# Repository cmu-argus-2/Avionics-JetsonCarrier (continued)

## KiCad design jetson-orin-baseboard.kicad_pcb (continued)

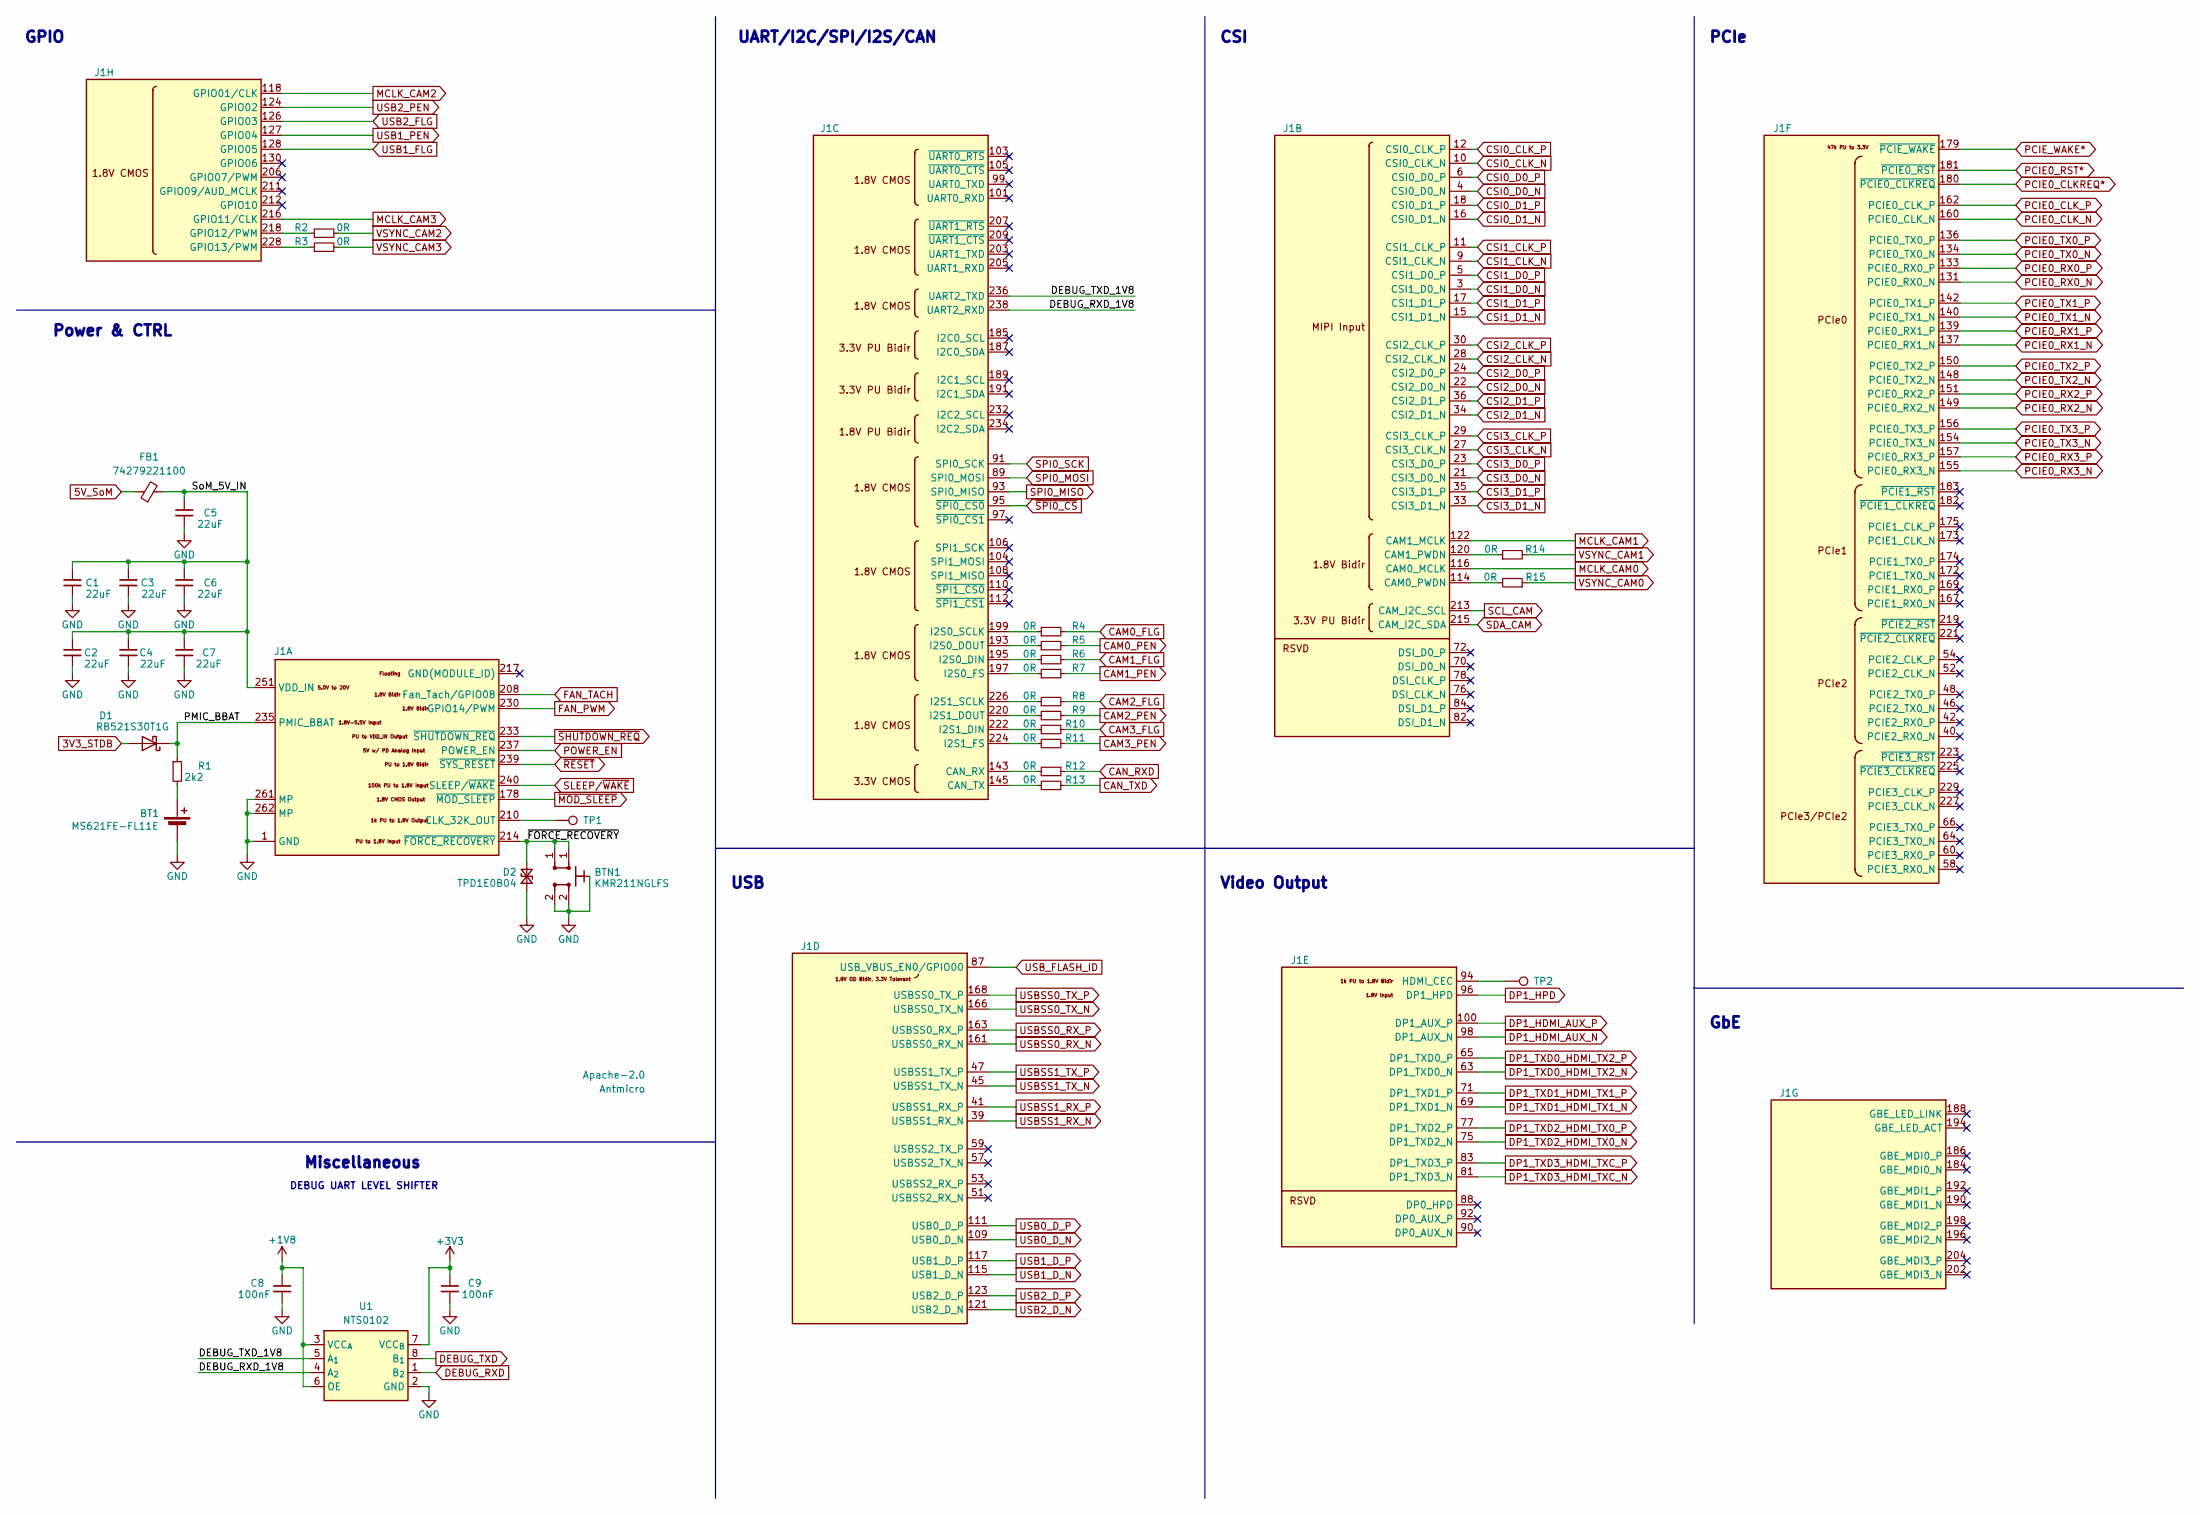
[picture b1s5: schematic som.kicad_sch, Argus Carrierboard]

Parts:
BT1: MS621FE-FL11E; MPN MS621FE-FL11E
BTN1: KMR211NGLFS; SW_Push_1P1T-SH_NO_CK_KMR2xxG; MPN C221676; LCSC C221676
C1, C2, C3, C4, C5, C6, C7: 22uF; C_0603_1608Metric; MPN C2762594; LCSC C84419
C8, C9: 100nF; C_0603_1608Metric; MPN C307348; LCSC C14663
D1: RB521S30T1G; D_SOD-523; MPN RB521S30T1G; LCSC C145179
D2: TPD1E0B04; Texas_DPY0002A_0.6x1mm_P0.65mm; MPN C1975594; LCSC C1975594
FB1: 74279221100; L_1206_3216Metric; MPN C5355985; LCSC C5355985
J1: Bus_DDR4_SODIMM_CUSTOM_Jetson-Orin-H9.2mm-socket; Jetson_Module_TE_2309409-1; MPN 2309413-1; LCSC C5164025
R1: 2k2; R_0603_1608Metric; MPN C2076947; LCSC C4190
R2, R3, R4, R5, R6, R7, R8, R9, R10, R11, R12, R13, R14, R15: 0R; R_0402_1005Metric; MPN C190119; LCSC C17168
TP1, TP2: TP_0.75mm_SMD; TestPoint_Pad_D1.0mm
U1: NTS0102; NXP_XSON-8; MPN NTS0102GT; LCSC C2687851

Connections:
3V3_STDB: D1.2 (A); also elsewhere on the board
5V_SoM: FB1.1; also elsewhere on the board
+1V8: C8.1, U1.3 (VCC_{A}), U1.6 (OE); also elsewhere on the board
+3V3: C9.1, U1.7 (VCC_{B}); also elsewhere on the board
/SoM/DEBUG_RXD_1V8: J1.238 (UART2_RXD), U1.4 (A_{2})
/SoM/DEBUG_TXD_1V8: J1.236 (UART2_TXD), U1.5 (A_{1})
/SoM/PMIC_BBAT: D1.1 (K), J1.235 (PMIC_BBAT), R1.1
/SoM/SoM_5V_IN: C1.1, C2.1, C3.1, C4.1, C5.1, C6.1, C7.1, FB1.2, J1.251 (VDD_IN), J1.252 (VDD_IN), J1.253 (VDD_IN), J1.254 (VDD_IN), J1.255 (VDD_IN), J1.256 (VDD_IN), J1.257 (VDD_IN), J1.258 (VDD_IN), J1.259 (VDD_IN), J1.260 (VDD_IN)
/SoM/~FORCE_RECOVERY: BTN1.1, D2.2 (A2), J1.214 (~FORCE_RECOVERY)
CAM0_FLG: R4.2; also elsewhere on the board
CAM0_PEN: R5.2; also elsewhere on the board
CAM1_FLG: R6.2; also elsewhere on the board
CAM1_PEN: R7.2; also elsewhere on the board
CAM2_FLG: R8.2; also elsewhere on the board
CAM2_PEN: R9.2; also elsewhere on the board
CAM3_FLG: R10.2; also elsewhere on the board
CAM3_PEN: R11.2; also elsewhere on the board
CAN_RXD: R12.2; also elsewhere on the board
CAN_TXD: R13.2; also elsewhere on the board
CSI0_CLK_N: J1.10 (CSI0_CLK_N); also elsewhere on the board
CSI0_CLK_P: J1.12 (CSI0_CLK_P); also elsewhere on the board
CSI0_D0_N: J1.4 (CSI0_D0_N); also elsewhere on the board
CSI0_D0_P: J1.6 (CSI0_D0_P); also elsewhere on the board
CSI0_D1_N: J1.16 (CSI0_D1_N); also elsewhere on the board
CSI0_D1_P: J1.18 (CSI0_D1_P); also elsewhere on the board
CSI1_CLK_N: J1.9 (CSI1_CLK_N); also elsewhere on the board
CSI1_CLK_P: J1.11 (CSI1_CLK_P); also elsewhere on the board
CSI1_D0_N: J1.3 (CSI1_D0_N); also elsewhere on the board
CSI1_D0_P: J1.5 (CSI1_D0_P); also elsewhere on the board
CSI1_D1_N: J1.15 (CSI1_D1_N); also elsewhere on the board
CSI1_D1_P: J1.17 (CSI1_D1_P); also elsewhere on the board
CSI2_CLK_N: J1.28 (CSI2_CLK_N); also elsewhere on the board
CSI2_CLK_P: J1.30 (CSI2_CLK_P); also elsewhere on the board
CSI2_D0_N: J1.22 (CSI2_D0_N); also elsewhere on the board
CSI2_D0_P: J1.24 (CSI2_D0_P); also elsewhere on the board
CSI2_D1_N: J1.34 (CSI2_D1_N); also elsewhere on the board
CSI2_D1_P: J1.36 (CSI2_D1_P); also elsewhere on the board
CSI3_CLK_N: J1.27 (CSI3_CLK_N); also elsewhere on the board
CSI3_CLK_P: J1.29 (CSI3_CLK_P); also elsewhere on the board
CSI3_D0_N: J1.21 (CSI3_D0_N); also elsewhere on the board
CSI3_D0_P: J1.23 (CSI3_D0_P); also elsewhere on the board
CSI3_D1_N: J1.33 (CSI3_D1_N); also elsewhere on the board
CSI3_D1_P: J1.35 (CSI3_D1_P); also elsewhere on the board
DEBUG_RXD: U1.1 (B_{2}); also elsewhere on the board
DEBUG_TXD: U1.8 (B_{1}); also elsewhere on the board
DP1_HDMI_AUX_N: J1.98 (DP1_AUX_N); also elsewhere on the board
DP1_HDMI_AUX_P: J1.100 (DP1_AUX_P); also elsewhere on the board
DP1_HPD: J1.96 (DP1_HPD); also elsewhere on the board
DP1_TXD0_HDMI_TX2_N: J1.63 (DP1_TXD0_N); also elsewhere on the board
DP1_TXD0_HDMI_TX2_P: J1.65 (DP1_TXD0_P); also elsewhere on the board
DP1_TXD1_HDMI_TX1_N: J1.69 (DP1_TXD1_N); also elsewhere on the board
DP1_TXD1_HDMI_TX1_P: J1.71 (DP1_TXD1_P); also elsewhere on the board
DP1_TXD2_HDMI_TX0_N: J1.75 (DP1_TXD2_N); also elsewhere on the board
DP1_TXD2_HDMI_TX0_P: J1.77 (DP1_TXD2_P); also elsewhere on the board
DP1_TXD3_HDMI_TXC_N: J1.81 (DP1_TXD3_N); also elsewhere on the board
DP1_TXD3_HDMI_TXC_P: J1.83 (DP1_TXD3_P); also elsewhere on the board
FAN_PWM: J1.230 (GPIO14/PWM); also elsewhere on the board
FAN_TACH: J1.208 (Fan_Tach/GPIO08); also elsewhere on the board
GND: BT1.2 (-), BTN1.2, BTN1.SH, C1.2, C2.2, C3.2, C4.2, C5.2, C6.2, C7.2, C8.2, C9.2, D2.1 (A1), J1.1 (GND), J1.2 (GND), J1.7 (GND), J1.8 (GND), J1.13 (GND), J1.14 (GND), J1.19 (GND), J1.20 (GND), J1.25 (GND), J1.26 (GND), J1.31 (GND), J1.32 (GND), J1.37 (GND), J1.38 (GND), J1.43 (GND), J1.44 (GND), J1.49 (GND), J1.50 (GND), J1.55 (GND), J1.56 (GND), J1.61 (GND), J1.62 (GND), J1.67 (GND), J1.68 (GND), J1.73 (GND), J1.74 (GND), J1.79 (GND), J1.80 (GND), J1.85 (GND), J1.86 (GND), J1.102 (GND), J1.107 (GND), J1.113 (GND), J1.119 (GND), J1.125 (GND), J1.129 (GND), J1.132 (GND), J1.135 (GND), J1.138 (GND), J1.141 (GND), J1.144 (GND), J1.146 (GND), J1.147 (GND), J1.152 (GND), J1.153 (GND), J1.158 (GND), J1.159 (GND), J1.164 (GND), J1.165 (GND), J1.170 (GND), J1.171 (GND), J1.176 (GND), J1.177 (GND), J1.200 (GND), J1.201 (GND), J1.231 (GND), J1.241 (GND), J1.242 (GND), J1.243 (GND), J1.244 (GND), J1.245 (GND), J1.246 (GND), J1.247 (GND), J1.248 (GND), J1.249 (GND), J1.250 (GND), J1.261 (MP), J1.262 (MP), U1.2 (GND); also elsewhere on the board
MCLK_CAM0: J1.116 (CAM0_MCLK); also elsewhere on the board
MCLK_CAM1: J1.122 (CAM1_MCLK); also elsewhere on the board
MCLK_CAM2: J1.118 (GPIO01/CLK); also elsewhere on the board
MCLK_CAM3: J1.216 (GPIO11/CLK); also elsewhere on the board
unnamed: BT1.1 (+), R1.2
unnamed: J1.210 (CLK_32K_OUT), TP1.1 (1_1)
unnamed: J1.114 (CAM0_PWDN), R15.2
unnamed: J1.120 (CAM1_PWDN), R14.1
unnamed: J1.143 (CAN_RX), R12.1
unnamed: J1.145 (CAN_TX), R13.1
unnamed: J1.195 (I2S0_DIN), R6.1
unnamed: J1.193 (I2S0_DOUT), R5.1
unnamed: J1.197 (I2S0_FS), R7.1
unnamed: J1.199 (I2S0_SCLK), R4.1
unnamed: J1.222 (I2S1_DIN), R10.1
unnamed: J1.220 (I2S1_DOUT), R9.1
unnamed: J1.224 (I2S1_FS), R11.1
unnamed: J1.226 (I2S1_SCLK), R8.1
unnamed: J1.94 (HDMI_CEC), TP2.1 (1_1)
unnamed: J1.218 (GPIO12/PWM), R2.1
unnamed: J1.228 (GPIO13/PWM), R3.1
PCIE0_CLKREQ*: J1.180 (~PCIE0_CLKREQ); also elsewhere on the board
PCIE0_CLK_N: J1.160 (PCIE0_CLK_N); also elsewhere on the board
PCIE0_CLK_P: J1.162 (PCIE0_CLK_P); also elsewhere on the board
PCIE0_RST*: J1.181 (~PCIE0_RST); also elsewhere on the board
PCIE0_RX0_N: J1.131 (PCIE0_RX0_N); also elsewhere on the board
PCIE0_RX0_P: J1.133 (PCIE0_RX0_P); also elsewhere on the board
PCIE0_RX1_N: J1.137 (PCIE0_RX1_N); also elsewhere on the board
PCIE0_RX1_P: J1.139 (PCIE0_RX1_P); also elsewhere on the board
PCIE0_RX2_N: J1.149 (PCIE0_RX2_N); also elsewhere on the board
PCIE0_RX2_P: J1.151 (PCIE0_RX2_P); also elsewhere on the board
PCIE0_RX3_N: J1.155 (PCIE0_RX3_N); also elsewhere on the board
PCIE0_RX3_P: J1.157 (PCIE0_RX3_P); also elsewhere on the board
PCIE0_TX0_N: J1.134 (PCIE0_TX0_N); also elsewhere on the board
PCIE0_TX0_P: J1.136 (PCIE0_TX0_P); also elsewhere on the board
PCIE0_TX1_N: J1.140 (PCIE0_TX1_N); also elsewhere on the board
PCIE0_TX1_P: J1.142 (PCIE0_TX1_P); also elsewhere on the board
PCIE0_TX2_N: J1.148 (PCIE0_TX2_N); also elsewhere on the board
PCIE0_TX2_P: J1.150 (PCIE0_TX2_P); also elsewhere on the board
PCIE0_TX3_N: J1.154 (PCIE0_TX3_N); also elsewhere on the board
PCIE0_TX3_P: J1.156 (PCIE0_TX3_P); also elsewhere on the board
PCIE_WAKE*: J1.179 (~PCIE_WAKE); also elsewhere on the board
POWER_EN: J1.237 (POWER_EN); also elsewhere on the board
SCL_CAM: J1.213 (CAM_I2C_SCL); also elsewhere on the board
SDA_CAM: J1.215 (CAM_I2C_SDA); also elsewhere on the board
SLEEP/~WAKE: J1.240 (SLEEP/~WAKE); also elsewhere on the board
SPI0_MISO: J1.93 (SPI0_MISO); also elsewhere on the board
SPI0_MOSI: J1.89 (SPI0_MOSI); also elsewhere on the board
SPI0_SCK: J1.91 (SPI0_SCK); also elsewhere on the board
USB0_D_N: J1.109 (USB0_D_N); also elsewhere on the board
USB0_D_P: J1.111 (USB0_D_P); also elsewhere on the board
USB1_D_N: J1.115 (USB1_D_N); also elsewhere on the board
USB1_D_P: J1.117 (USB1_D_P); also elsewhere on the board
USB1_FLG: J1.128 (GPIO05); also elsewhere on the board
USB1_PEN: J1.127 (GPIO04); also elsewhere on the board
USB2_D_N: J1.121 (USB2_D_N); also elsewhere on the board
USB2_D_P: J1.123 (USB2_D_P); also elsewhere on the board
USB2_FLG: J1.126 (GPIO03); also elsewhere on the board
USB2_PEN: J1.124 (GPIO02); also elsewhere on the board
USBSS0_RX_N: J1.161 (USBSS0_RX_N); also elsewhere on the board
USBSS0_RX_P: J1.163 (USBSS0_RX_P); also elsewhere on the board
USBSS0_TX_N: J1.166 (USBSS0_TX_N); also elsewhere on the board
USBSS0_TX_P: J1.168 (USBSS0_TX_P); also elsewhere on the board
USBSS1_RX_N: J1.39 (USBSS1_RX_N); also elsewhere on the board
USBSS1_RX_P: J1.41 (USBSS1_RX_P); also elsewhere on the board
USBSS1_TX_N: J1.45 (USBSS1_TX_N); also elsewhere on the board
USBSS1_TX_P: J1.47 (USBSS1_TX_P); also elsewhere on the board
USB_FLASH_ID: J1.87 (USB_VBUS_EN0/GPIO00); also elsewhere on the board
VSYNC_CAM0: R15.1; also elsewhere on the board
VSYNC_CAM1: R14.2; also elsewhere on the board
VSYNC_CAM2: R2.2; also elsewhere on the board
VSYNC_CAM3: R3.2; also elsewhere on the board
~MOD_SLEEP: J1.178 (~MOD_SLEEP); also elsewhere on the board
~RESET: J1.239 (~SYS_RESET); also elsewhere on the board
~SHUTDOWN_REQ: J1.233 (~SHUTDOWN_REQ); also elsewhere on the board
~SPI0_CS: J1.95 (~SPI0_CS0); also elsewhere on the board

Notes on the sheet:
DEBUG UART LEVEL SHIFTER
CSI
Video Output
Power & CTRL
UART/I2C/SPI/I2S/CAN
PCIe
GbE
USB
GPIO
Miscellaneous

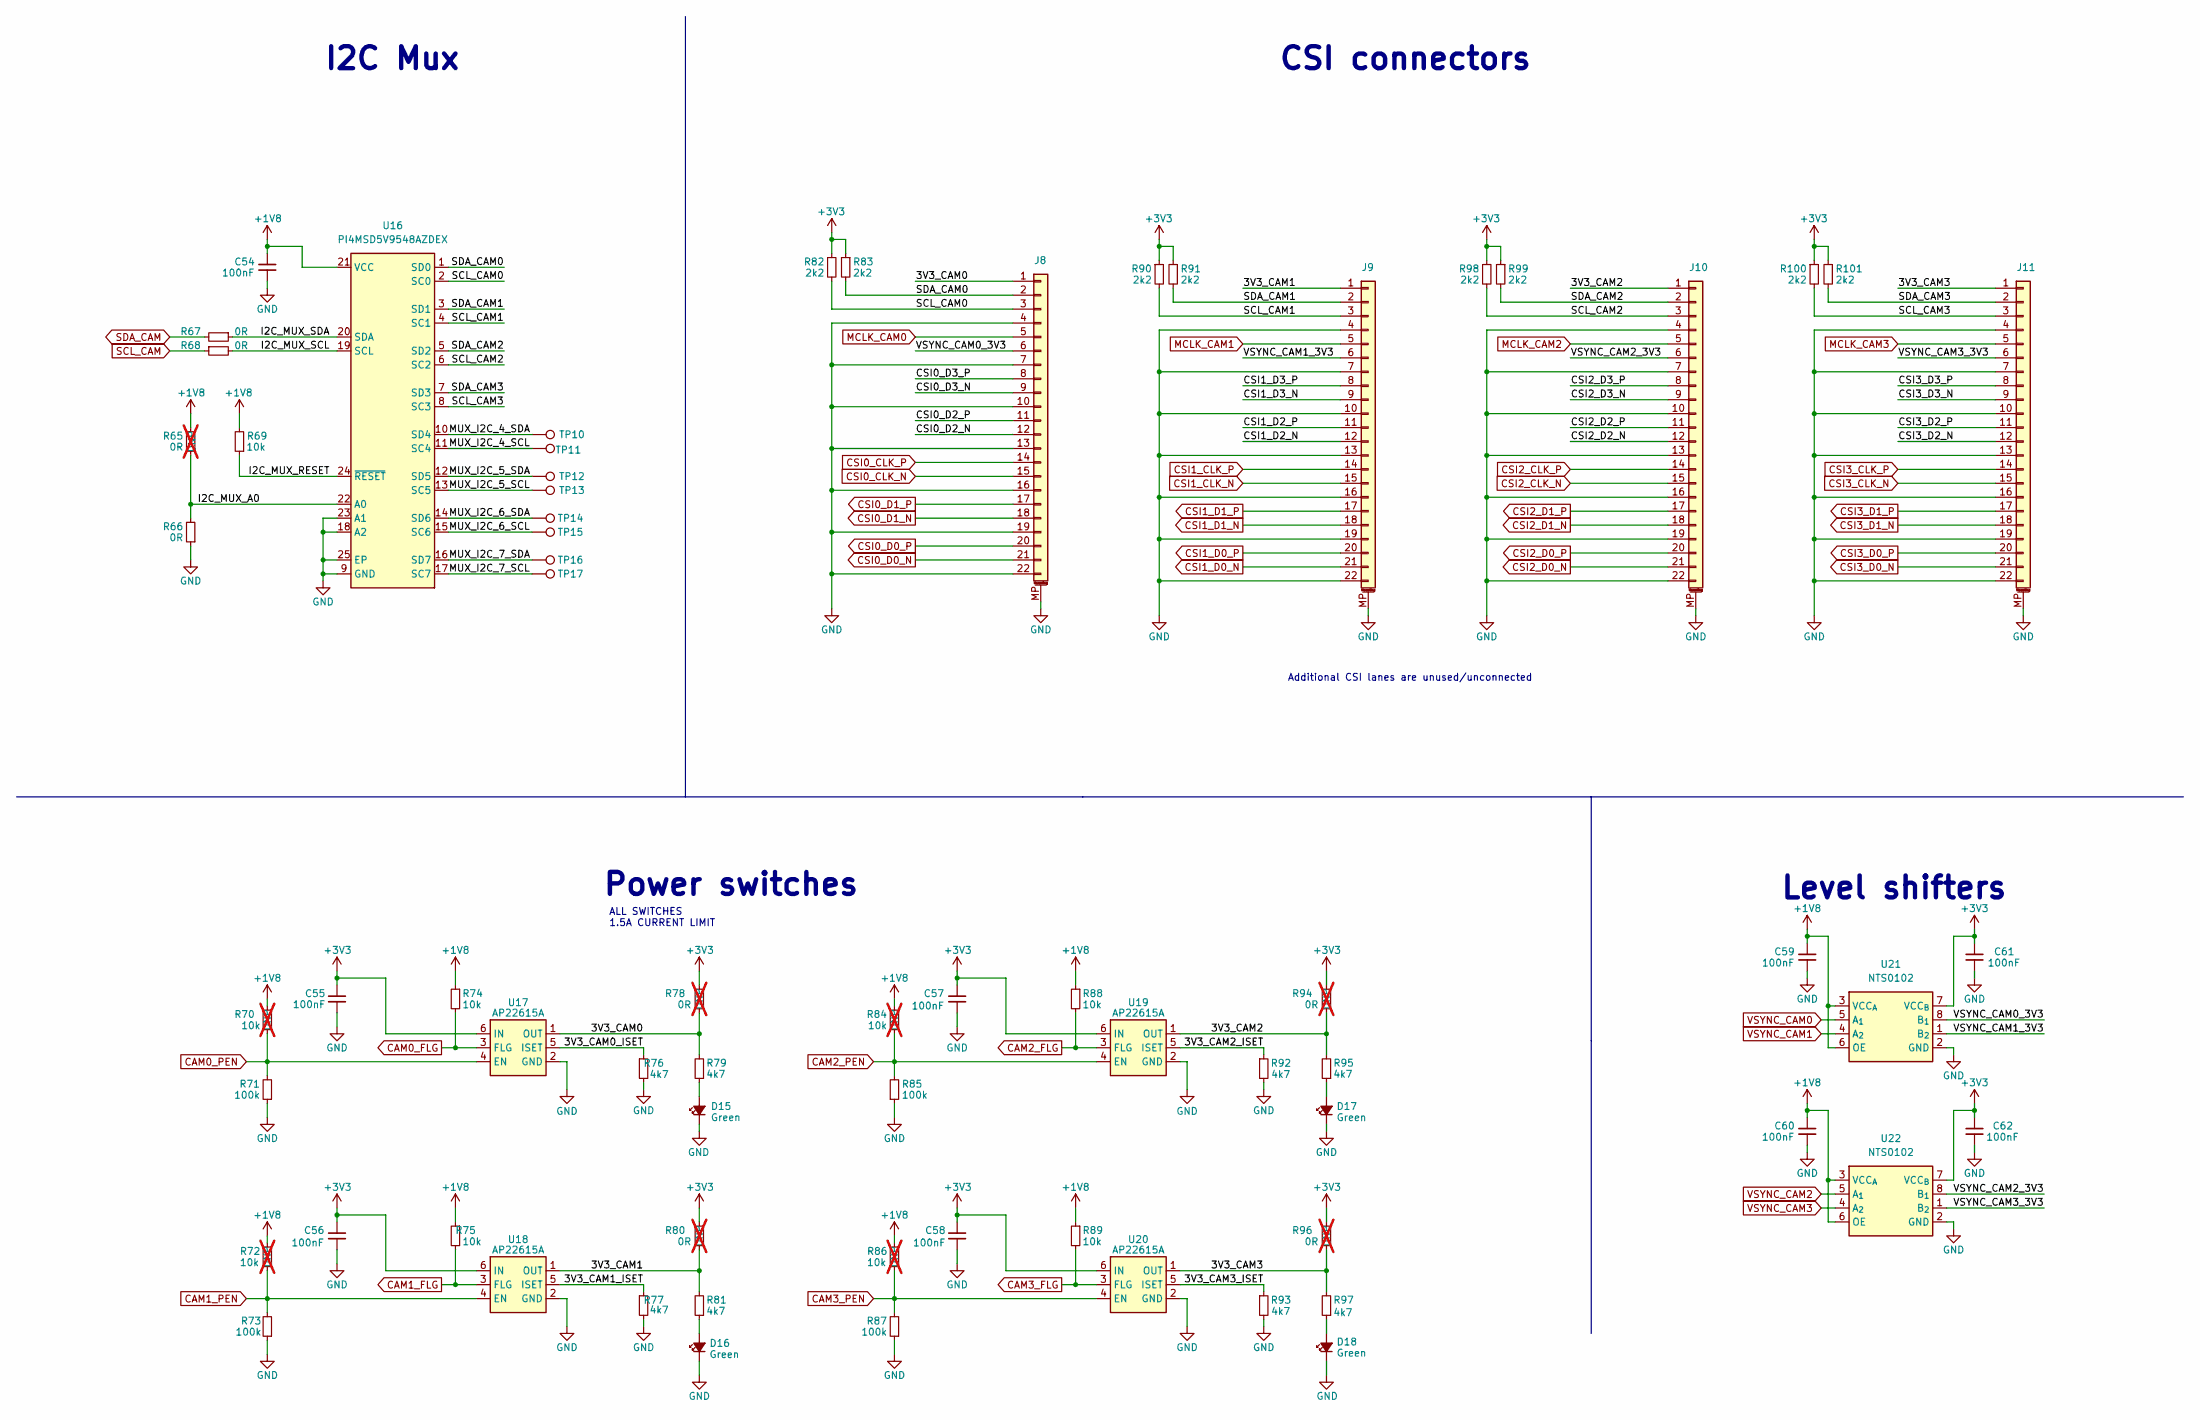
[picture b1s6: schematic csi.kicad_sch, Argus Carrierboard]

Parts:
C54, C55, C56, C57, C58, C59, C60, C61, C62: 100nF; C_0603_1608Metric; MPN C307348; LCSC C14663
D15, D16, D17, D18: LED_G_0603_LTST-C190GKT; LED_0603_1608Metric; MPN C2909774; LCSC C12065
J8, J9, J10, J11: Conn_01x22_MountingPin; Amphenol_F32Q-1A7x1-11022_1x22-1MP_P0.5mm_Horizontal
R65: 0R; R_0402_1005Metric; MPN ERJ2GE0R00X; LCSC C17168; not fitted
R66, R67, R68: 0R; R_0402_1005Metric; MPN C190119; LCSC C17168
R69, R74, R75, R88, R89: 10k; R_0603_1608Metric; MPN C2479067; LCSC C25804
R70, R72, R84, R86: 10k; R_0603_1608Metric; Tolerance 1%; MPN CR0402-FX-1002GLF; LCSC C25804; not fitted
R71, R73, R85, R87: 100k; R_0603_1608Metric; MPN C237792; LCSC C25803
R76, R77, R79, R81, R92, R93, R95, R97: 4k7; R_0603_1608Metric; MPN C844931; LCSC C23162
R78, R80, R94, R96: 0R; R_0603_1608Metric; Tolerance 1%; MPN CR0402-FX-1002GLF; LCSC C21189; not fitted
R82, R83, R90, R91, R98, R99, R100, R101: 2k2; R_0603_1608Metric; MPN C2076947; LCSC C4190
TP10, TP11, TP12, TP13, TP14, TP15, TP16, TP17: TP_0.75mm_SMD; TestPoint_Pad_D1.0mm
U16: PI4MSD5V9548AZDEX; TQFN-24-1EP_4x4mm_P0.5mm_EP2.3x2.3mm; MPN PI4MSD5V9548AZDEX; LCSC C2674581
U17, U18, U19, U20: AP22615A; TSOT-23-6; MPN C2680357; LCSC C2680357
U21, U22: NTS0102; NXP_XSON-8; MPN NTS0102GT; LCSC C2687851

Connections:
+1V8: C54.2, C59.1, C60.1, R65.2, R69.2, R70.1, R72.1, R74.1, R75.1, R84.1, R86.1, R88.1, R89.1, U16.21 (VCC), U21.3 (VCC_{A}), U21.6 (OE), U22.3 (VCC_{A}), U22.6 (OE); also elsewhere on the board
+3V3: C55.2, C56.2, C57.2, C58.2, C61.1, C62.1, R78.1, R80.1, R82.1, R83.1, R90.1, R91.1, R94.1, R96.1, R98.1, R99.1, R100.1, R101.1, U17.6 (IN), U18.6 (IN), U19.6 (IN), U20.6 (IN), U21.7 (VCC_{B}), U22.7 (VCC_{B}); also elsewhere on the board
/CSI/3V3_CAM0: J8.1, R78.2, R79.2, U17.1 (OUT)
/CSI/3V3_CAM0_ISET: R76.1, U17.5 (ISET)
/CSI/3V3_CAM1: J9.1, R80.2, R81.2, U18.1 (OUT)
/CSI/3V3_CAM1_ISET: R77.1, U18.5 (ISET)
/CSI/3V3_CAM2: J10.1, R94.2, R95.2, U19.1 (OUT)
/CSI/3V3_CAM2_ISET: R92.1, U19.5 (ISET)
/CSI/3V3_CAM3: J11.1, R96.2, R97.2, U20.1 (OUT)
/CSI/3V3_CAM3_ISET: R93.1, U20.5 (ISET)
/CSI/CSI0_D2_N: J8.12
/CSI/CSI0_D2_P: J8.11
/CSI/CSI0_D3_N: J8.9
/CSI/CSI0_D3_P: J8.8
/CSI/CSI1_D2_N: J9.12
/CSI/CSI1_D2_P: J9.11
/CSI/CSI1_D3_N: J9.9
/CSI/CSI1_D3_P: J9.8
/CSI/CSI2_D2_N: J10.12
/CSI/CSI2_D2_P: J10.11
/CSI/CSI2_D3_N: J10.9
/CSI/CSI2_D3_P: J10.8
/CSI/CSI3_D2_N: J11.12
/CSI/CSI3_D2_P: J11.11
/CSI/CSI3_D3_N: J11.9
/CSI/CSI3_D3_P: J11.8
/CSI/I2C_MUX_A0: R65.1, R66.2, U16.22 (A0)
/CSI/I2C_MUX_RESET: R69.1, U16.24 (~RESET)
/CSI/I2C_MUX_SCL: R68.2, U16.19 (SCL)
/CSI/I2C_MUX_SDA: R67.1, U16.20 (SDA)
/CSI/MUX_I2C_4_SCL: TP11.1 (1_1), U16.11 (SC4)
/CSI/MUX_I2C_4_SDA: TP10.1 (1_1), U16.10 (SD4)
/CSI/MUX_I2C_5_SCL: TP13.1 (1_1), U16.13 (SC5)
/CSI/MUX_I2C_5_SDA: TP12.1 (1_1), U16.12 (SD5)
/CSI/MUX_I2C_6_SCL: TP15.1 (1_1), U16.15 (SC6)
/CSI/MUX_I2C_6_SDA: TP14.1 (1_1), U16.14 (SD6)
/CSI/MUX_I2C_7_SCL: TP17.1 (1_1), U16.17 (SC7)
/CSI/MUX_I2C_7_SDA: TP16.1 (1_1), U16.16 (SD7)
/CSI/SCL_CAM0: J8.3, R82.2, U16.2 (SC0)
/CSI/SCL_CAM1: J9.3, R90.2, U16.4 (SC1)
/CSI/SCL_CAM2: J10.3, R98.2, U16.6 (SC2)
/CSI/SCL_CAM3: J11.3, R100.2, U16.8 (SC3)
/CSI/SDA_CAM0: J8.2, R83.2, U16.1 (SD0)
/CSI/SDA_CAM1: J9.2, R91.2, U16.3 (SD1)
/CSI/SDA_CAM2: J10.2, R99.2, U16.5 (SD2)
/CSI/SDA_CAM3: J11.2, R101.2, U16.7 (SD3)
/CSI/VSYNC_CAM0_3V3: J8.6, U21.8 (B_{1})
/CSI/VSYNC_CAM1_3V3: J9.6, U21.1 (B_{2})
/CSI/VSYNC_CAM2_3V3: J10.6, U22.8 (B_{1})
/CSI/VSYNC_CAM3_3V3: J11.6, U22.1 (B_{2})
CAM0_FLG: R74.2, U17.3 (FLG); also elsewhere on the board
CAM0_PEN: R70.2, R71.2, U17.4 (EN); also elsewhere on the board
CAM1_FLG: R75.2, U18.3 (FLG); also elsewhere on the board
CAM1_PEN: R72.2, R73.2, U18.4 (EN); also elsewhere on the board
CAM2_FLG: R88.2, U19.3 (FLG); also elsewhere on the board
CAM2_PEN: R84.2, R85.2, U19.4 (EN); also elsewhere on the board
CAM3_FLG: R89.2, U20.3 (FLG); also elsewhere on the board
CAM3_PEN: R86.2, R87.2, U20.4 (EN); also elsewhere on the board
CSI0_CLK_N: J8.15; also elsewhere on the board
CSI0_CLK_P: J8.14; also elsewhere on the board
CSI0_D0_N: J8.21; also elsewhere on the board
CSI0_D0_P: J8.20; also elsewhere on the board
CSI0_D1_N: J8.18; also elsewhere on the board
CSI0_D1_P: J8.17; also elsewhere on the board
CSI1_CLK_N: J9.15; also elsewhere on the board
CSI1_CLK_P: J9.14; also elsewhere on the board
CSI1_D0_N: J9.21; also elsewhere on the board
CSI1_D0_P: J9.20; also elsewhere on the board
CSI1_D1_N: J9.18; also elsewhere on the board
CSI1_D1_P: J9.17; also elsewhere on the board
CSI2_CLK_N: J10.15; also elsewhere on the board
CSI2_CLK_P: J10.14; also elsewhere on the board
CSI2_D0_N: J10.21; also elsewhere on the board
CSI2_D0_P: J10.20; also elsewhere on the board
CSI2_D1_N: J10.18; also elsewhere on the board
CSI2_D1_P: J10.17; also elsewhere on the board
CSI3_CLK_N: J11.15; also elsewhere on the board
CSI3_CLK_P: J11.14; also elsewhere on the board
CSI3_D0_N: J11.21; also elsewhere on the board
CSI3_D0_P: J11.20; also elsewhere on the board
CSI3_D1_N: J11.18; also elsewhere on the board
CSI3_D1_P: J11.17; also elsewhere on the board
GND: C54.1, C55.1, C56.1, C57.1, C58.1, C59.2, C60.2, C61.2, C62.2, D15.1 (K), D16.1 (K), D17.1 (K), D18.1 (K), J8.4, J8.7, J8.10, J8.13, J8.16, J8.19, J8.22, J8.MP (MountPin), J9.4, J9.7, J9.10, J9.13, J9.16, J9.19, J9.22, J9.MP (MountPin), J10.4, J10.7, J10.10, J10.13, J10.16, J10.19, J10.22, J10.MP (MountPin), J11.4, J11.7, J11.10, J11.13, J11.16, J11.19, J11.22, J11.MP (MountPin), R66.1, R71.1, R73.1, R76.2, R77.2, R85.1, R87.1, R92.2, R93.2, U16.9 (GND), U16.18 (A2), U16.23 (A1), U16.25 (EP), U17.2 (GND), U18.2 (GND), U19.2 (GND), U20.2 (GND), U21.2 (GND), U22.2 (GND); also elsewhere on the board
MCLK_CAM0: J8.5; also elsewhere on the board
MCLK_CAM1: J9.5; also elsewhere on the board
MCLK_CAM2: J10.5; also elsewhere on the board
MCLK_CAM3: J11.5; also elsewhere on the board
unnamed: D15.2 (A), R79.1
unnamed: D16.2 (A), R81.1
unnamed: D17.2 (A), R95.1
unnamed: D18.2 (A), R97.1
SCL_CAM: R68.1; also elsewhere on the board
SDA_CAM: R67.2; also elsewhere on the board
VSYNC_CAM0: U21.5 (A_{1}); also elsewhere on the board
VSYNC_CAM1: U21.4 (A_{2}); also elsewhere on the board
VSYNC_CAM2: U22.5 (A_{1}); also elsewhere on the board
VSYNC_CAM3: U22.4 (A_{2}); also elsewhere on the board

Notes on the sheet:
Power switches
CSI connectors
Additional CSI lanes are unused/unconnected
I2C Mux
ALL SWITCHES 1.5A CURRENT LIMIT
Level shifters

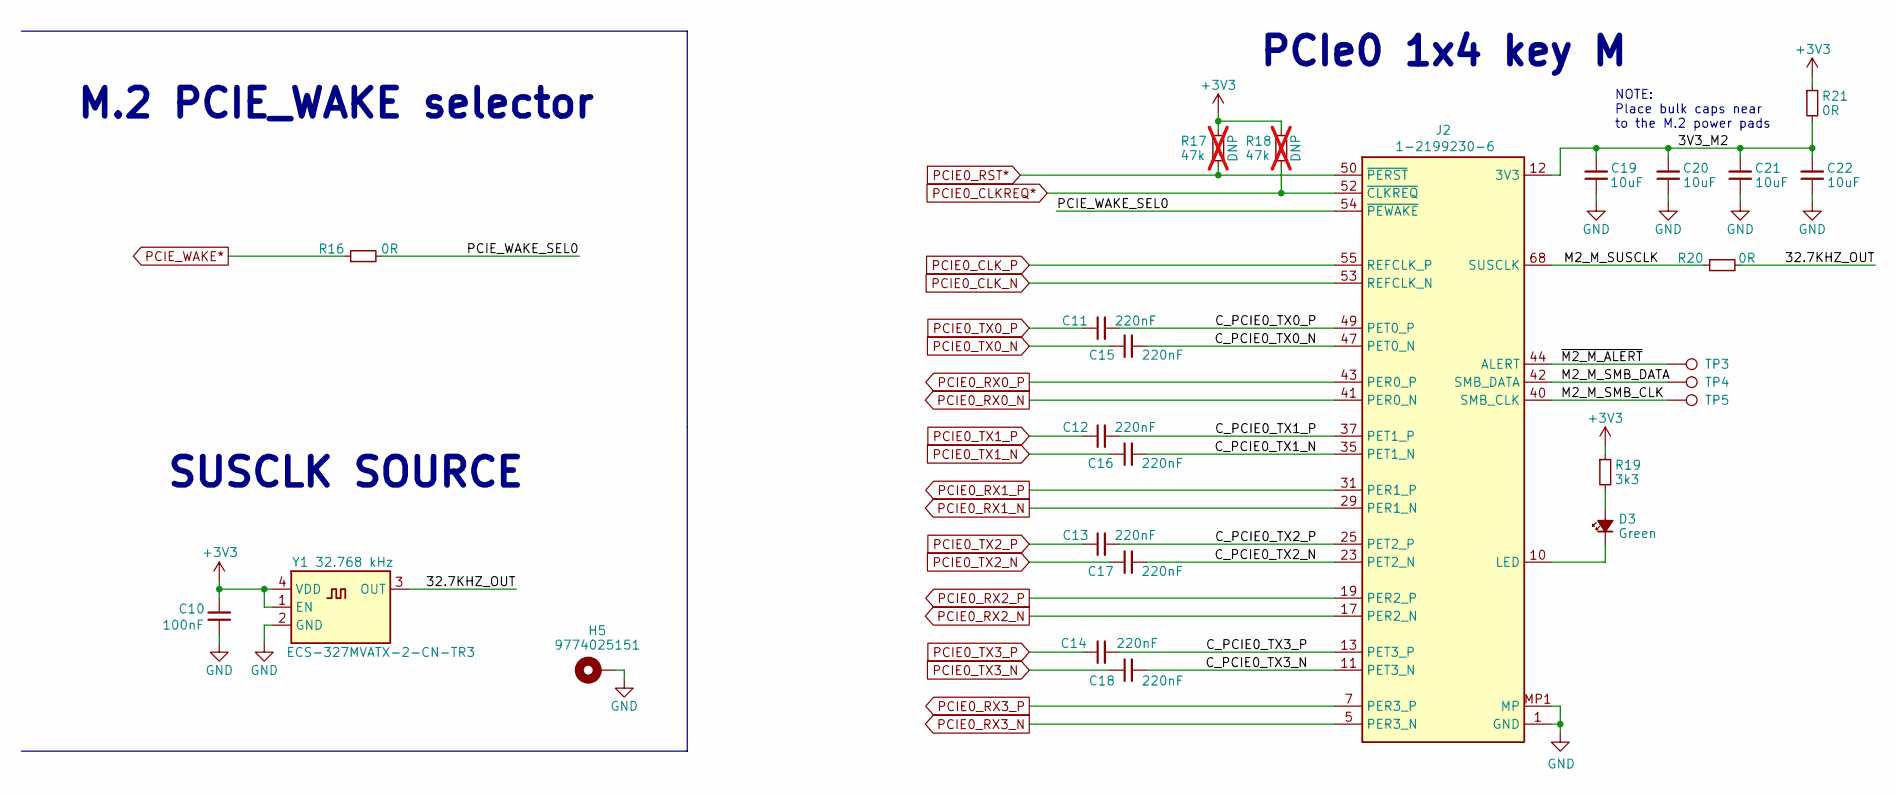
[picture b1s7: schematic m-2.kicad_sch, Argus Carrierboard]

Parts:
C10: 100nF; C_0603_1608Metric; MPN C307348; LCSC C14663
C11, C12, C13, C14, C15, C16, C17, C18: 220nF; C_0402_1005Metric; MPN C126623; LCSC C16772
C19, C20, C21, C22: 10uF; C_0603_1608Metric; MPN C697423; LCSC C96446
D3: LED_G_0603_LTST-C190GKT; LED_0603_1608Metric; MPN C2909774; LCSC C12065
H5: 9774025151; MountingHole_2.7mm_M2.5_DIN965_Pad_TopBottom; MPN 9774025151R
J2: 1-2199230-6; Bus_M.2_Socket_Key_M_TE_1-2199230-6; MPN C4710843; LCSC C4710843
R16, R20: 0R; R_0402_1005Metric; MPN C190119; LCSC C17168
R17, R18: 47k; R_0402_1005Metric; Tolerance 1%; MPN CR0402-FX-4702GLF; LCSC C25792; not fitted
R19: 3k3; R_0603_1608Metric; MPN C844928; LCSC C22978
R21: 0R; R_0603_1608Metric; MPN C844915; LCSC C21189
TP3, TP4, TP5: TP_0.75mm_SMD; TestPoint_Pad_D1.0mm
Y1: ECS-327MVATX-2-CN-TR3; Oscillator_SMD_ECS_2520MV_2.5x2mm; MPN ECS-327MVATX-2-CN-TR3; LCSC C5375606

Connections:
+3V3: C10.2, R17.1, R18.1, R19.1, R21.1, Y1.1 (EN), Y1.4 (VDD); also elsewhere on the board
/M.2/3V3_M2: C19.1, C20.1, C21.1, C22.1, J2.2 (3V3), J2.4 (3V3), J2.12 (3V3), J2.14 (3V3), J2.16 (3V3), J2.18 (3V3), J2.70 (3V3), J2.72 (3V3), J2.74 (3V3), R21.2
/M.2/32.7KHZ_OUT: R20.2, Y1.3 (OUT)
/M.2/C_PCIE0_TX0_N: C15.2, J2.47 (PET0_N)
/M.2/C_PCIE0_TX0_P: C11.2, J2.49 (PET0_P)
/M.2/C_PCIE0_TX1_N: C16.1, J2.35 (PET1_N)
/M.2/C_PCIE0_TX1_P: C12.1, J2.37 (PET1_P)
/M.2/C_PCIE0_TX2_N: C17.1, J2.23 (PET2_N)
/M.2/C_PCIE0_TX2_P: C13.1, J2.25 (PET2_P)
/M.2/C_PCIE0_TX3_N: C18.2, J2.11 (PET3_N)
/M.2/C_PCIE0_TX3_P: C14.1, J2.13 (PET3_P)
/M.2/M2_M_SMB_CLK: J2.40 (SMB_CLK), TP5.1 (1_1)
/M.2/M2_M_SMB_DATA: J2.42 (SMB_DATA), TP4.1 (1_1)
/M.2/M2_M_SUSCLK: J2.68 (SUSCLK), R20.1
/M.2/PCIE_WAKE_SEL0: J2.54 (~PEWAKE), R16.2
/M.2/~M2_M_ALERT: J2.44 (ALERT), TP3.1 (1_1)
GND: C10.1, C19.2, C20.2, C21.2, C22.2, H5.1 (1_1), J2.1 (GND), J2.3 (GND), J2.9 (GND), J2.15 (GND), J2.21 (GND), J2.27 (GND), J2.33 (GND), J2.39 (GND), J2.45 (GND), J2.51 (GND), J2.57 (GND), J2.71 (GND), J2.73 (GND), J2.75 (GND), J2.MP1 (MP), J2.MP2 (MP), Y1.2 (GND); also elsewhere on the board
unnamed: D3.2 (A), R19.2
unnamed: D3.1 (K), J2.10 (LED)
PCIE0_CLKREQ*: J2.52 (~CLKREQ), R18.2; also elsewhere on the board
PCIE0_CLK_N: J2.53 (REFCLK_N); also elsewhere on the board
PCIE0_CLK_P: J2.55 (REFCLK_P); also elsewhere on the board
PCIE0_RST*: J2.50 (~PERST), R17.2; also elsewhere on the board
PCIE0_RX0_N: J2.41 (PER0_N); also elsewhere on the board
PCIE0_RX0_P: J2.43 (PER0_P); also elsewhere on the board
PCIE0_RX1_N: J2.29 (PER1_N); also elsewhere on the board
PCIE0_RX1_P: J2.31 (PER1_P); also elsewhere on the board
PCIE0_RX2_N: J2.17 (PER2_N); also elsewhere on the board
PCIE0_RX2_P: J2.19 (PER2_P); also elsewhere on the board
PCIE0_RX3_N: J2.5 (PER3_N); also elsewhere on the board
PCIE0_RX3_P: J2.7 (PER3_P); also elsewhere on the board
PCIE0_TX0_N: C15.1; also elsewhere on the board
PCIE0_TX0_P: C11.1; also elsewhere on the board
PCIE0_TX1_N: C16.2; also elsewhere on the board
PCIE0_TX1_P: C12.2; also elsewhere on the board
PCIE0_TX2_N: C17.2; also elsewhere on the board
PCIE0_TX2_P: C13.2; also elsewhere on the board
PCIE0_TX3_N: C18.1; also elsewhere on the board
PCIE0_TX3_P: C14.2; also elsewhere on the board
PCIE_WAKE*: R16.1; also elsewhere on the board

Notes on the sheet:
M.2 PCIE_WAKE selector
PCIe0 1x4 key M
NOTE: Place bulk caps near to the M.2 power pads
SUSCLK SOURCE
